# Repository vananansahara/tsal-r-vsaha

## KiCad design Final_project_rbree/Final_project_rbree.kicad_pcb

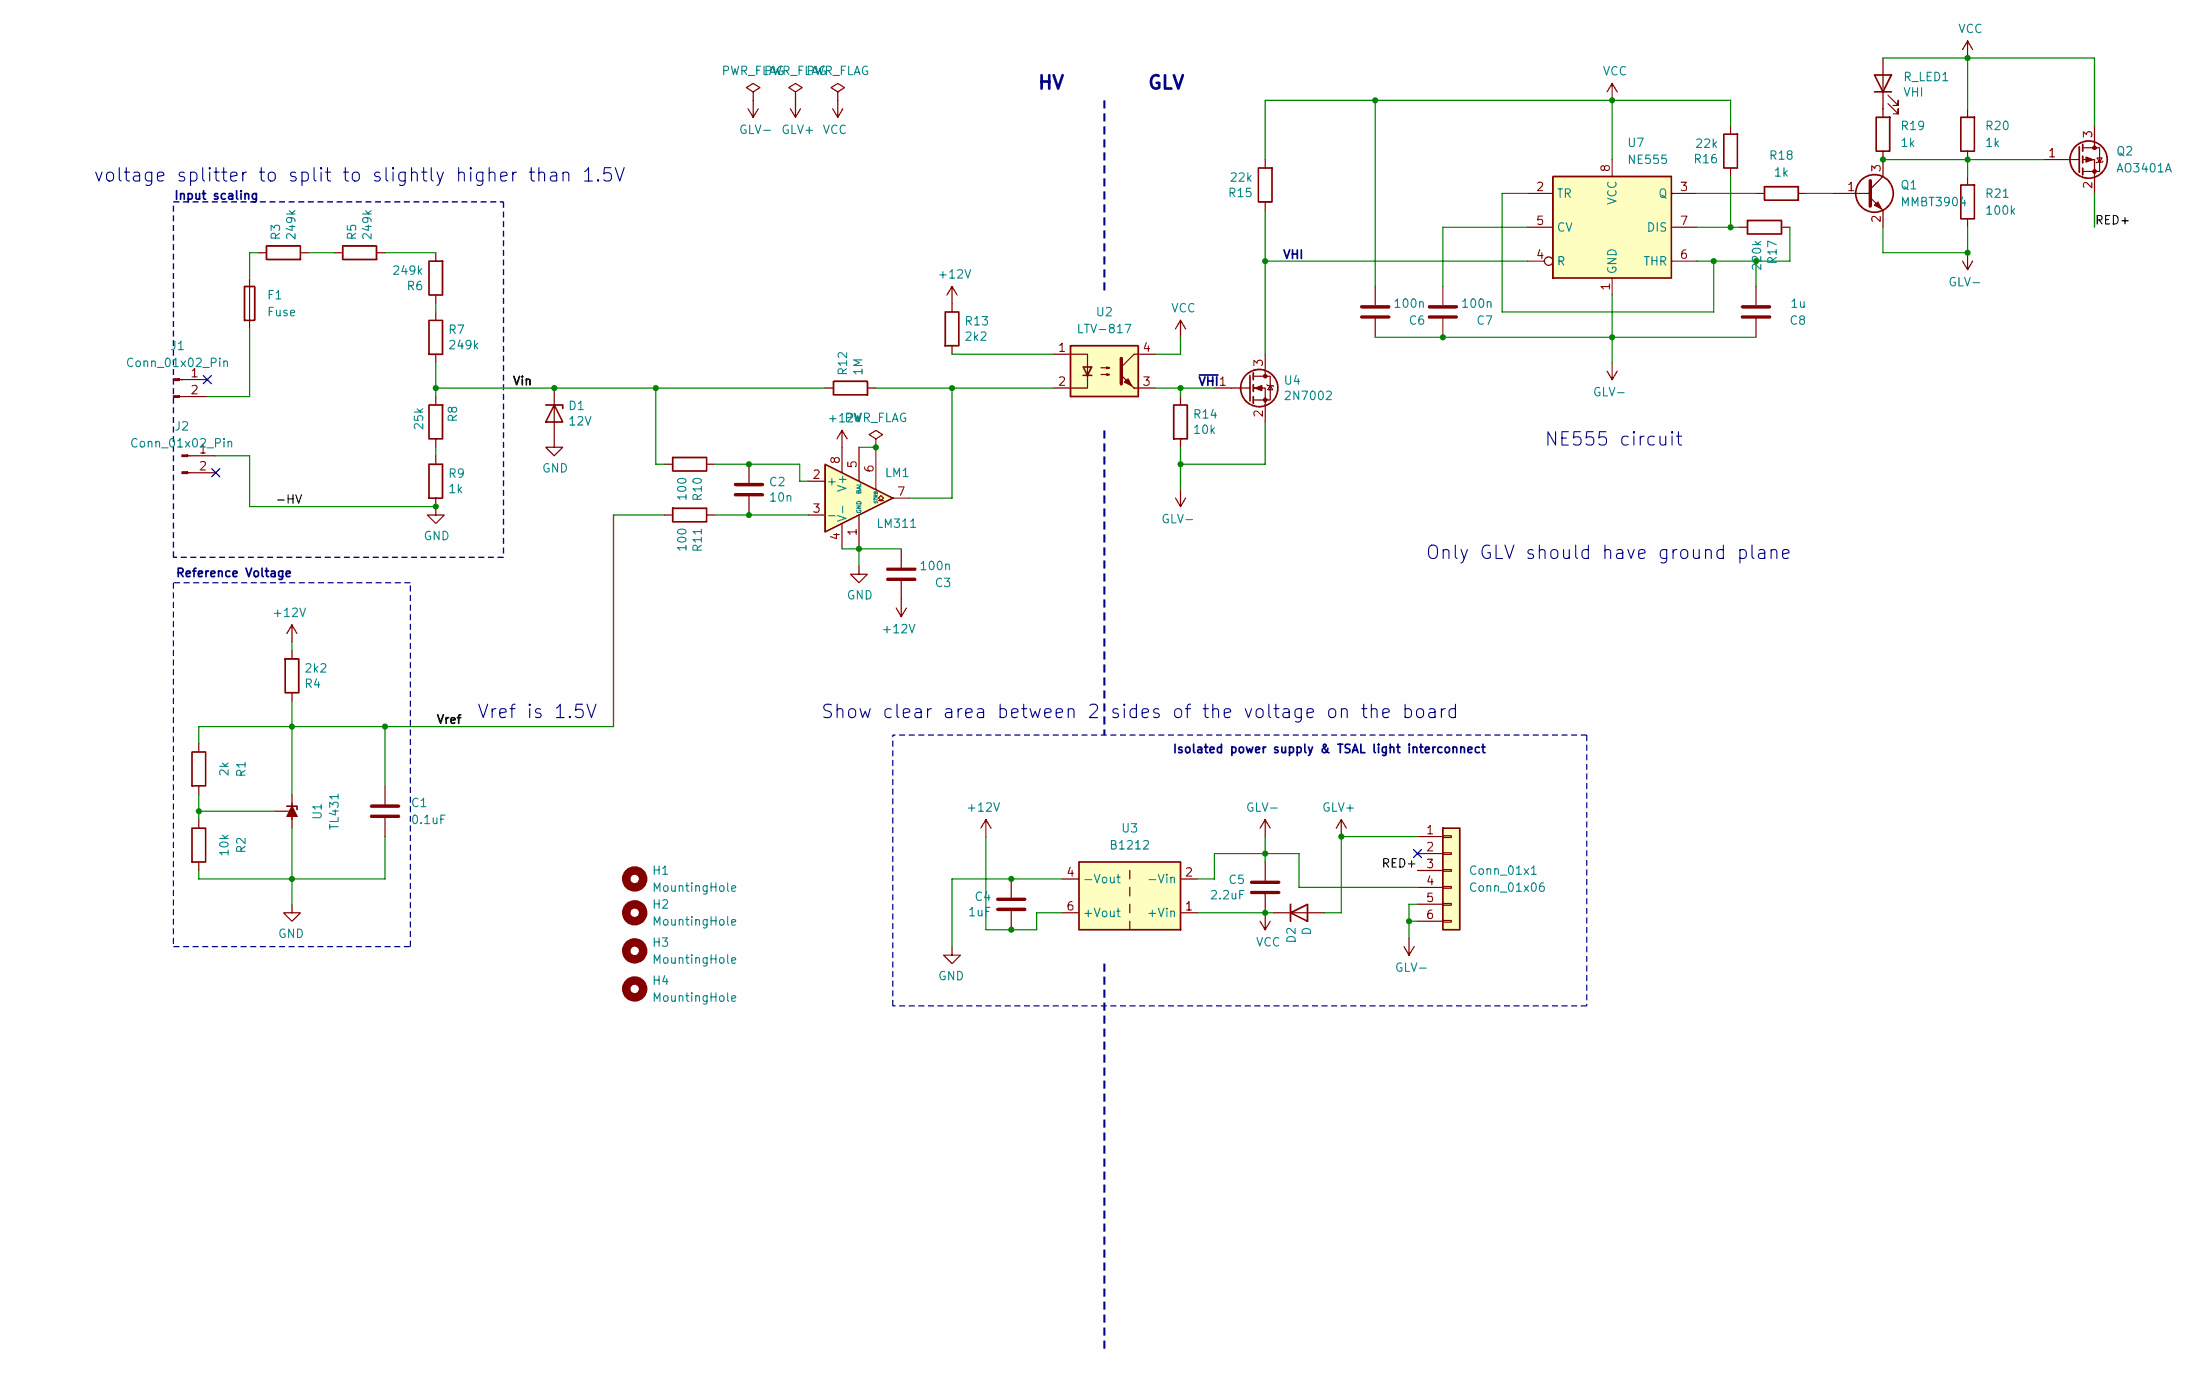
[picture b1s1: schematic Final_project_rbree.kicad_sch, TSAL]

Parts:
C1: 0.1uF; C_0805_2012Metric
C2: 10n; C_0805_2012Metric
C3, C6, C7: 100n; C_0805_2012Metric
C4: 1uF; C_0805_2012Metric
C5: 2.2uF; C_0805_2012Metric
C8: 1u; C_0805_2012Metric
Conn_01x1: Conn_01x06; JST_VH_B6P-VH_1x06_P3.96mm_Vertical
D1: 12V; D_DO-35_SOD27_P7.62mm_Horizontal
D2: D; D_SMA
F1: Fuse; Fuse_1210_3225Metric
H1, H2, H3, H4: MountingHole; MountingHole_3.2mm_M3
J1, J2: Conn_01x02_Pin; AMASS_XT60-M_1x02_P7.20mm_Vertical
LM1: LM311; DIP-8_W10.16mm
Q1: MMBT3904; SOT-23
Q2: AO3401A; SOT-23
R1: 2k; R_0805_2012Metric
R2, R14: 10k; R_0805_2012Metric
R3, R5, R6, R7: 249k; R_0805_2012Metric
R4, R13: 2k2; R_0805_2012Metric
R8: 25k; R_0805_2012Metric
R9, R18, R19, R20: 1k; R_0805_2012Metric
R10, R11: 100; R_0805_2012Metric
R12: 1M; R_0805_2012Metric
R15, R16: 22k; R_0805_2012Metric
R17: 220k; R_0805_2012Metric
R21: 100k; R_0805_2012Metric
R_LED1: VHI; LED_0805_2012Metric
U1: TL431; TO-92_Inline
U2: LTV-817; DIP-4_W7.62mm
U3: B1212; Converter_DCDC_TRACO_TBA2-xxxx_Single_THT
U4: 2N7002; SOT-23
U7: NE555; SOIC-8_3.9x4.9mm_P1.27mm

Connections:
+12V: C3.1, C4.2, LM1.8 (V+), R4.2, R13.1, U3.6 (+Vout)
/RED+: Conn_01x1.3, Q2.2 (S)
/Vin: D1.1 (K), R7.2, R8.2, R10.2, R12.1
/Vref: C1.1, R1.1, R4.1, R11.2, U1.3 (K)
GLV+: Conn_01x1.1, D2.2 (A)
GLV-: C5.1, C6.1, C7.1, C8.1, Conn_01x1.4, Conn_01x1.5, Conn_01x1.6, Q1.2 (E), R14.2, R21.1, U3.2 (-Vin), U4.2 (S), U7.1 (GND)
GND: C1.2, C3.2, C4.1, D1.2 (A), J2.1, LM1.1 (GND), LM1.4 (V-), R2.2, R9.2, U1.2 (A), U3.4 (-Vout)
unnamed: F1.1, R3.1
unnamed: F1.2, J1.2
unnamed: C2.1, LM1.2 (+), R10.1
unnamed: C2.2, LM1.3 (-), R11.1
unnamed: LM1.5 (BAL), LM1.6 (STRB)
unnamed: LM1.7, R12.2, U2.2
unnamed: Q1.1 (B), R18.2
unnamed: Q1.3 (C), Q2.1 (G), R19.1, R20.1, R21.2
unnamed: R3.2, R5.1
unnamed: R5.2, R6.2
unnamed: R6.1, R7.1
unnamed: R8.1, R9.1
unnamed: R13.2, U2.1
unnamed: R19.2, R_LED1.1 (K)
unnamed: R1.2, R2.1, U1.1 (REF)
unnamed: R15.1, U4.3 (D), U7.4 (R)
unnamed: R14.1, U2.3, U4.1 (G)
unnamed: C7.2, U7.5 (CV)
unnamed: R16.1, R17.2, U7.7 (DIS)
unnamed: R18.1, U7.3 (Q)
unnamed: C8.2, R17.1, U7.2 (TR), U7.6 (THR)
VCC: C5.2, C6.2, D2.1 (K), Q2.3 (D), R15.2, R16.2, R20.2, R_LED1.2 (A), U2.4, U3.1 (+Vin), U7.8 (VCC)

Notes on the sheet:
voltage splitter to split to slightly higher than 1.5V
Show clear area between 2 sides of the voltage on the board
Isolated power supply & TSAL light interconnect
Reference Voltage
~{VHI}
Input scaling
Only GLV should have ground plane
GLV
VHI
Vref is 1.5V
NE555 circuit

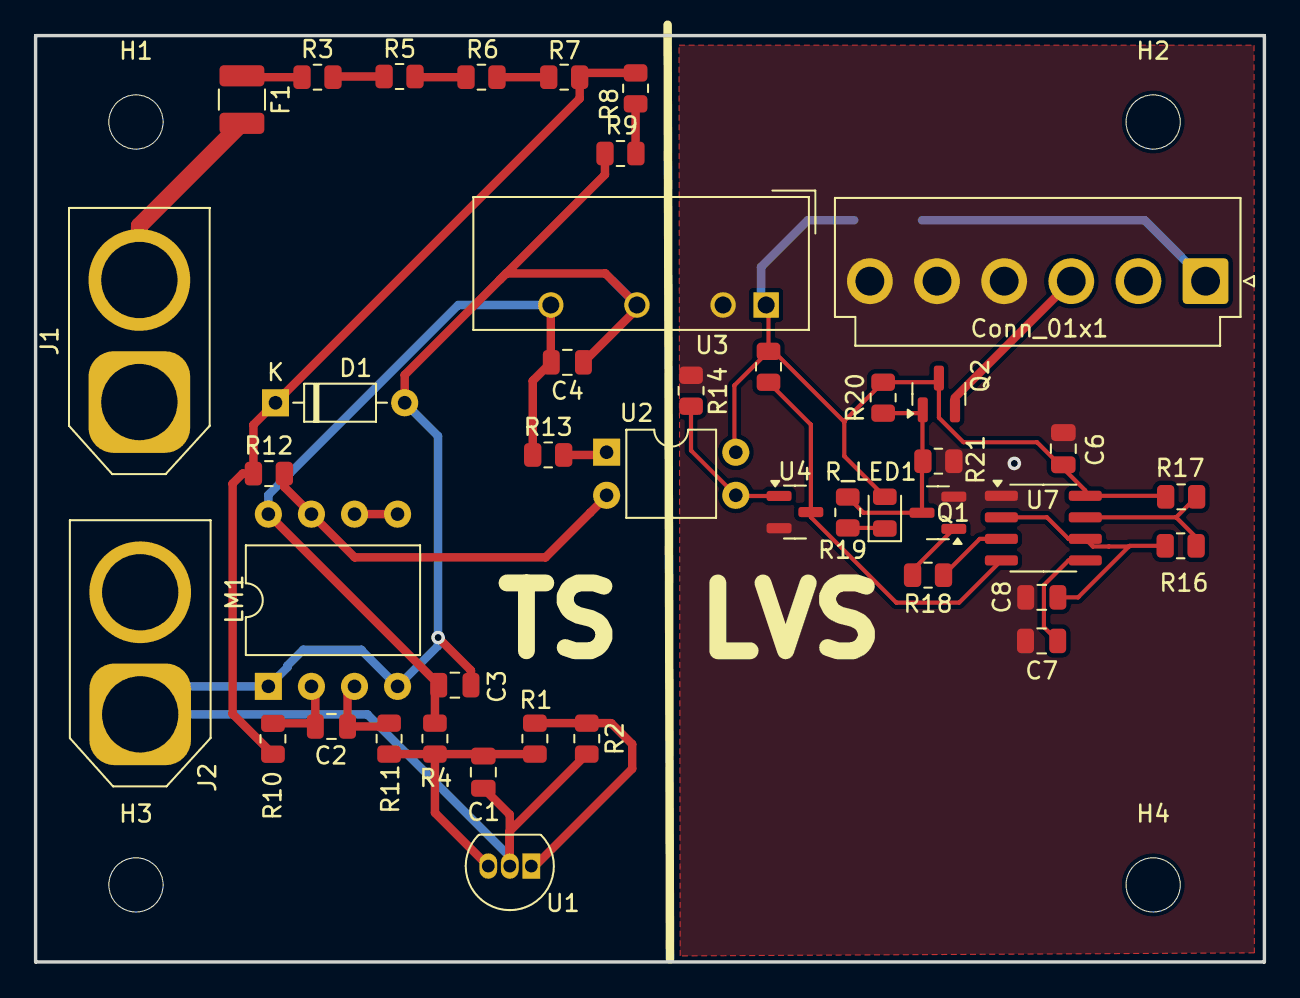
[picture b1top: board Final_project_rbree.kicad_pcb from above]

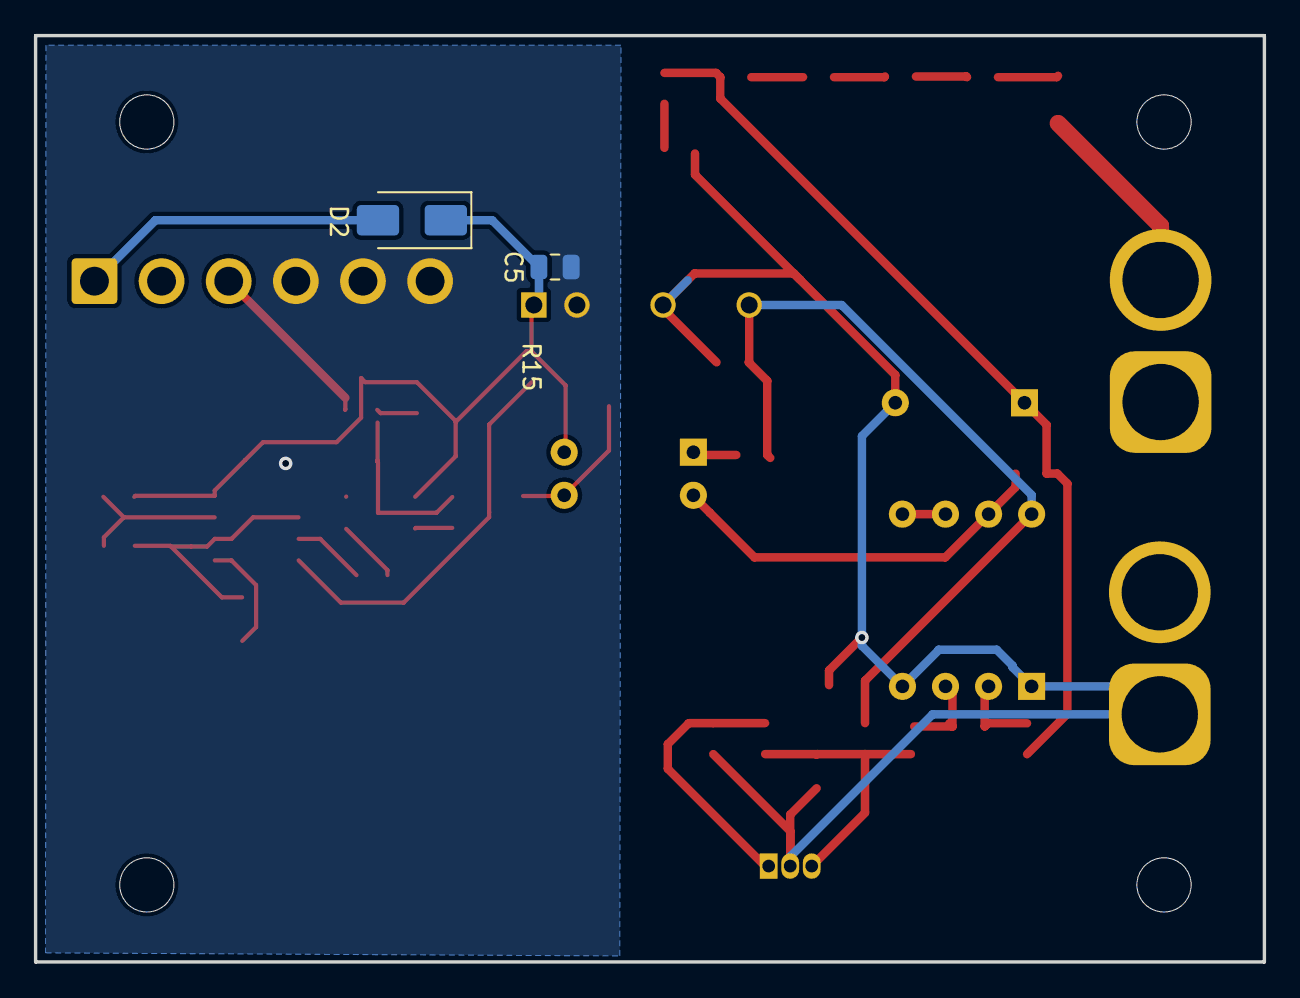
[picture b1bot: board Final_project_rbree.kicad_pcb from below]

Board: 2 copper layers, 72.5 x 54.6 mm, 48 parts (2 on the bottom side), 29 nets.
